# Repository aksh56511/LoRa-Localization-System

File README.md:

# LoRa Localization System

This project implements a LoRa-based localization system using RSSI and directional antenna scanning.

## 📡 Overview
The system detects the direction of a signal source using RSSI values from a LoRa module. A servo motor rotates the antenna, and multiple readings are used for triangulation.

## ⚙️ Components
- STM32 Microcontroller
- LoRa SX1276 Module
- Servo Motor
- Capacitors & Resistors

## 🧠 Working
- LoRa receives signal strength (RSSI)
- STM32 processes data
- Servo rotates antenna (PWM control)
- MATLAB estimates location using triangulation

## 🖥️ Tools Used
- KiCad (PCB Design)
- MATLAB (Simulation)

## 📊 Output
- RSSI vs Angle graph
- Estimated beacon position
- PCB layout

## 📷 Project Images

## 👨‍💻 Author
Aksh

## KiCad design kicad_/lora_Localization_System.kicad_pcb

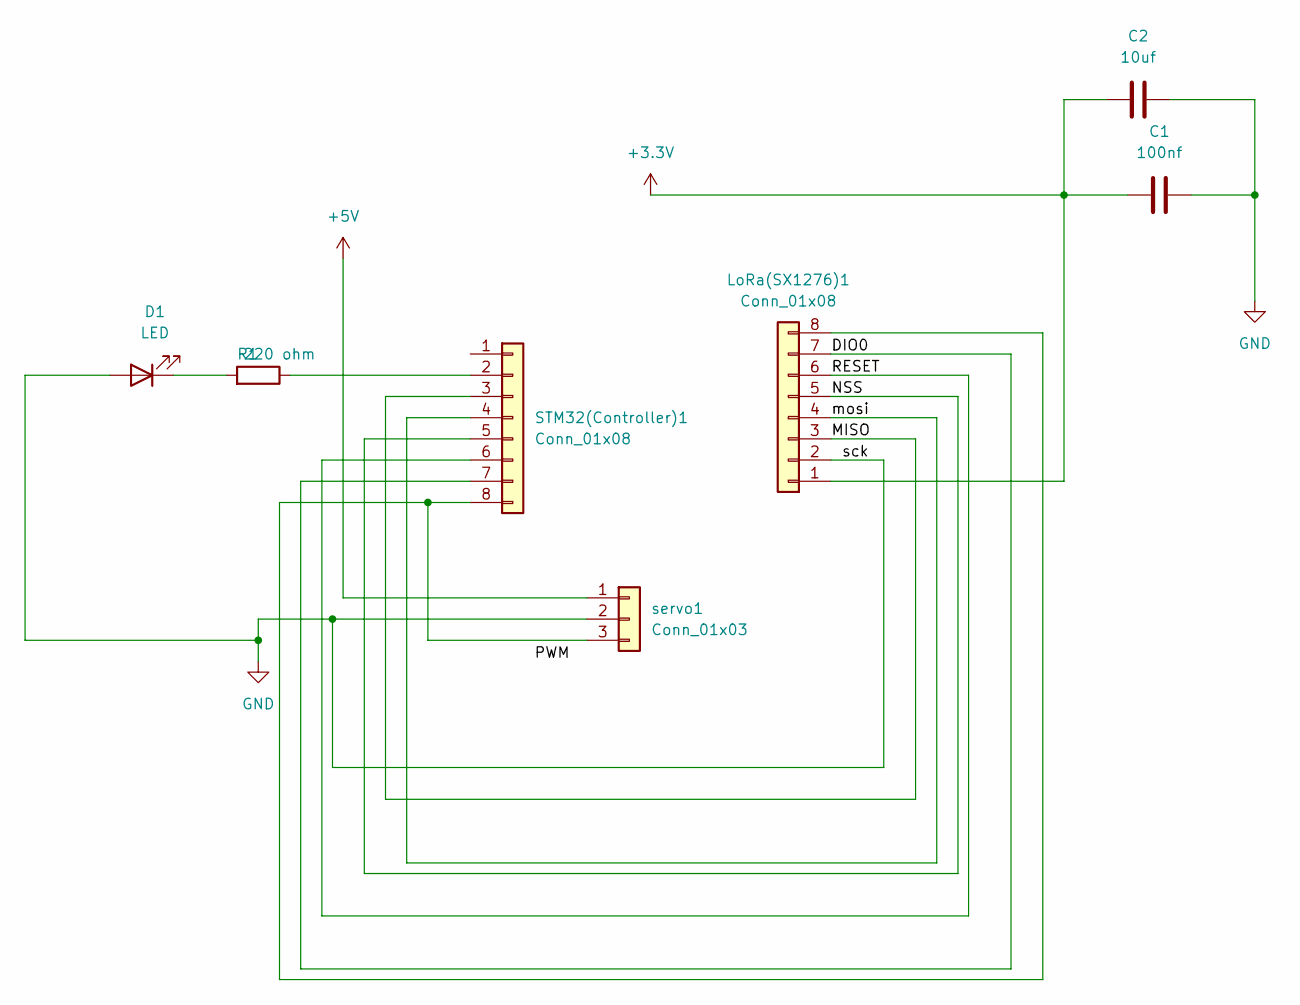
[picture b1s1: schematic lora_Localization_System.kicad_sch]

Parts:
C1: 100nf; C_Disc_D5.0mm_W2.5mm_P5.00mm
C2: 10uf; C_Disc_D5.0mm_W2.5mm_P5.00mm
D1: LED; LED_D5.0mm
LoRa(SX1276)1: Conn_01x08; PinHeader_1x08_P2.54mm_Vertical
R1: 220 ohm; R_Axial_DIN0207_L6.3mm_D2.5mm_P7.62mm_Horizontal
STM32(Controller)1: Conn_01x08; PinHeader_1x08_P2.54mm_Vertical
servo1: Conn_01x03; PinHeader_1x08_P2.54mm_Vertical

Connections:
+3.3V: C1.1, C2.1, LoRa(SX1276)1.1
+5V: servo1.1
/DIO0: LoRa(SX1276)1.7, STM32(Controller)1.7
/MISO: LoRa(SX1276)1.3, STM32(Controller)1.3
/NSS: LoRa(SX1276)1.5, STM32(Controller)1.5
/RESET: LoRa(SX1276)1.6, STM32(Controller)1.6
/mosi: LoRa(SX1276)1.4, STM32(Controller)1.4
GND: C1.2, C2.2, D1.2 (A), LoRa(SX1276)1.2, servo1.2
unnamed: D1.1 (K), R1.2
unnamed: LoRa(SX1276)1.8, STM32(Controller)1.8, servo1.3
unnamed: R1.1, STM32(Controller)1.2

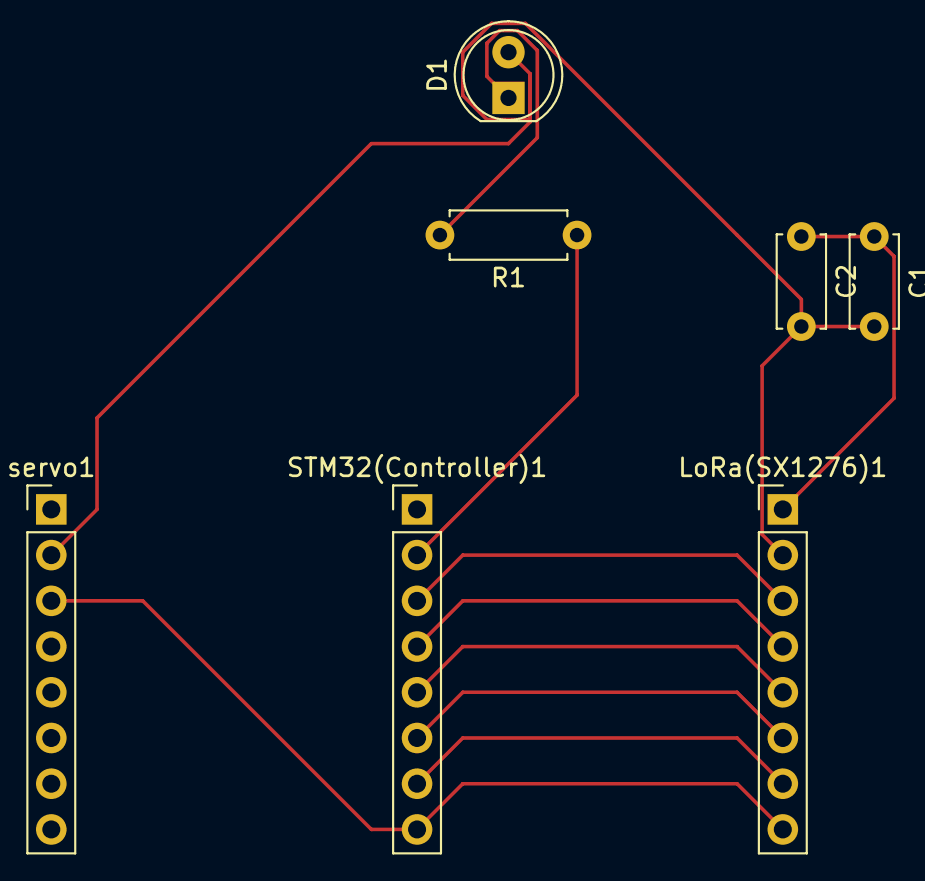
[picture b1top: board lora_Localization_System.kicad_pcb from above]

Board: 2 copper layers, 7 parts (0 on the bottom side), 10 nets.
